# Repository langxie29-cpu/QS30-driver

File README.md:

# QS30 驱动 — 九位模块化（REV.A9）

> 最新进度（2026-11-15）：[24V重构项目](projects/QS30-9_24V/README.md)、[S06B资格审查报告](projects/QS30-9_24V/docs/SPRINT06B_REPORT.md)及[S06C续作计划](projects/QS30-9_24V/docs/S06C_PLAN.md)。24V-07未通过、08未进入，制造HOLD；[工程进展与知识书稿](output/nxt_book/书稿.md)。仿真大文件恢复见[归档说明](docs9/SIMULATION_ARCHIVES.md)。

> 最新实测入口（2026-11-10–11）：[Electrical Closure Sprint 01](docs9/ELECTRICAL_CLOSURE_SPRINT01.md)。DRC 753→698，ERC 0错误/364警告；高压启动/保护仍FAIL/HOLD，禁止投板。

> **当前基线：QS30-9 / REV.A（九位 3+3+3 模块化）**
> 先读 [`docs9/FINAL_REPORT9.md`](docs9/FINAL_REPORT9.md)（A–G 报告）与
> [`docs9/AUDIT.md`](docs9/AUDIT.md)（旧六位审计/架构差异）、[`docs9/GATES.md`](docs9/GATES.md)（G0–G5）。
>
> - 架构/网表/ERC9：`docs9/ARCHITECTURE.md`、`netlist9/`、`docs9/ERC9.md`（**36/36 PASS**，规则级）
> - 电源重算/OVP 容差/泄放：`docs9/POWER9.md`
> - 驱动比较 / BOM-A/B/C / 成本：`docs9/DRIVER_COMPARE.md`、`bom9/`、`docs9/COST9.md`
> - 接口与 90 路映射：`docs9/interface9.csv`、`docs9/channel_map9.csv`（位序 PROVISIONAL）
> - 机械/PCB 尺寸：`docs9/MECH9.md`（结论：三管共板不进 100 mm 档，需支架或 100×150）
> - 未冻结项：`HOLD_REGISTER9.md`；问题：`open_issues9.md`
> - **未经授权不下单、不打样、不释放 Gerber；未验证项不得标为通过。**
> - 旧六位 REV.A 设计完整保留为 Legacy（见文末"Legacy"与 `legacy/REV6/README.md`，commit `52eaa95`）。

---

## Legacy：六位 REV.A（REV6）原始文档

# QS30-6 REV.A — 六位静态辉光钟（ESP32-S3 / 南昌 QS30-1 / 立创EDA）

**工程状态：HOLD —— 可继续 PCB 预布局与实物验证，禁止投板、禁止生产放行。**
本仓库是 REV.A 的**可复现设计输入 + 已执行的仿真/检查证据**，不是已签审的完整 EDA 工程。

- 设计输入：`QS30-6_REV.A_ESP32_QS30-1_立创EDA工程交接_修订01.docx`（旧交接，已全程审查）
- 本基线：REV.A r1（2026-10-18）
- 规模：**227 个器件 / 736 个引脚 / 172 个网络 / 60 路数字阴极 / 2×HV5622**
- 自动一致性检查：**19 项全部 PASS（0 ERROR / 0 WARN）**，见 `docs/erc_report.md`

---

## 0. 交接入口

**先读 [`docs/HANDOVER.md`](docs/HANDOVER.md)**：交付物索引、证据分级、HOLD 解除路径、
从零复现验证结果与"禁止投板"结论。

## 1. 交付物索引

| 类别 | 文件 |
|---|---|
| 设计决策 | [`design_decisions.md`](design_decisions.md) |
| 未关闭问题 | [`open_issues.md`](open_issues.md) |
| 资料登记 | [`source_register.md`](source_register.md) |
| 变更记录 | [`REV_A_CHANGELOG.md`](REV_A_CHANGELOG.md) |
| HOLD 闸门 | [`HOLD_REGISTER.md`](HOLD_REGISTER.md) |
| 网表（逐引脚，权威） | [`netlist/QS30-6_REV.A_netlist.csv`](netlist/QS30-6_REV.A_netlist.csv) ｜ [`netlist/QS30-6_REV.A_nets.csv`](netlist/QS30-6_REV.A_nets.csv) ｜ [`netlist/QS30-6_REV.A_netlist.json`](netlist/QS30-6_REV.A_netlist.json) |
| BOM | [`bom/QS30-6_REV.A_BOM.csv`](bom/QS30-6_REV.A_BOM.csv) ｜ 已验证子集 [`bom/QS30-6_REV.A_BOM_verified_only.csv`](bom/QS30-6_REV.A_BOM_verified_only.csv) |
| 通道映射 | [`docs/channel_mapping.csv`](docs/channel_mapping.csv) ｜ [`docs/schematic/QS30-6_REV.A_通道映射表.png`](docs/schematic/QS30-6_REV.A_通道映射表.png) |
| QS30-1 脚号映射 | [`docs/qs30_1_pin_mapping.csv`](docs/qs30_1_pin_mapping.csv) |
| 原理图（连接表式分页图 + PDF） | [`docs/schematic/QS30-6_REV.A_原理图连接表.pdf`](docs/schematic/QS30-6_REV.A_原理图连接表.pdf)（11 页：系统框图 + 9 页分页连接表 + 通道映射表）｜ `docs/schematic/page_01.png` … `page_09.png` |
| 系统框图 | [`docs/schematic/QS30-6_REV.A_系统框图.png`](docs/schematic/QS30-6_REV.A_系统框图.png) |
| PCB 预布局 | [`docs/prelayout/QS30-6_REV.A_prelayout.png`](docs/prelayout/QS30-6_REV.A_prelayout.png) ｜ `.pdf` |
| BOM 数量汇总（114 组，含 DNP） | [`bom/QS30-6_REV.A_BOM_qty.csv`](bom/QS30-6_REV.A_BOM_qty.csv) |
| 逐页网络清单（立创EDA 录入用） | `netlist/by_sheet/{01_PWR,02_MCU,03_DRV,04_HV,05_TUBE,06_TP}_nets.csv` |
| 符号↔焊盘↔原厂脚号总表（H09 证据） | [`docs/symbol_footprint_mapping.csv`](docs/symbol_footprint_mapping.csv) |
| PCB 规则矩阵（H07 占位） | [`docs/pcb_rule_matrix.csv`](docs/pcb_rule_matrix.csv) |
| ERC 记录 | [`docs/erc_report.md`](docs/erc_report.md) |
| **DRC 预检（网表级，14/14 PASS）** | [`docs/drc_precheck.md`](docs/drc_precheck.md) ｜ [`drc_precheck.json`](docs/drc_precheck.json) ｜ 脚本 [`design/drc_precheck.py`](design/drc_precheck.py) |
| **HOLD 进度看板** | [`docs/hold_dashboard.md`](docs/hold_dashboard.md)（填写进度 + 关键路径） |
| **HOLD 签署与关闭联动（本次新增）** | 签署表 [`docs/HOLD_SIGNOFF.csv`](docs/HOLD_SIGNOFF.csv) ｜ 报告 [`docs/hold_signoff_report.md`](docs/hold_signoff_report.md) |
| **HOLD 证据模板与自动校验** | 模板 [`docs/evidence/`](docs/evidence/README.md)（10 个 CSV，含期望值与判据）｜ 校验 [`design/evidence_check.py`](design/evidence_check.py) ｜ 状态报告 [`docs/hold_closure_report.md`](docs/hold_closure_report.md) ｜ 框架自测 [`docs/evidence_selftest.md`](docs/evidence_selftest.md) |
| 立创EDA 构建步骤 | [`docs/lceda_implementation_guide.md`](docs/lceda_implementation_guide.md) |
| 上电验证计划 | [`docs/test_plan.md`](docs/test_plan.md) |
| 升压/OVP 仿真 | [`sim/README.md`](sim/README.md) ｜ 结果 `sim/results/`（6 张图 + 10 份 CSV + summary.json + convergence） |
| **平均模型闭环仿真** | `sim/boost_averaged.cir` ／ `sim/boost_averaged_steps.cir` ｜ 结果 [`sim/results/spice_averaged_closed_loop.png`](sim/results/spice_averaged_closed_loop.png) |
| **OVP 保护逻辑 SPICE** | `sim/boost_ovp_logic.cir` ｜ 结果 [`sim/results/spice_ovp_latch.png`](sim/results/spice_ovp_latch.png)（触发/锁存/泄放/复位/再触发，7 项判据） |
| **OVP 时序回归（本次新增）** | 复位脉冲宽度/锁存保持扫描：`design/ovp_timing_scan.py` ｜ [`docs/ovp_timing.md`](docs/ovp_timing.md) |
| **测试计划一致性检查** | `docs/test_plan.csv`（37 项机读）＋ `design/test_plan_check.py` ｜ [`docs/test_plan_check.md`](docs/test_plan_check.md) 5/5 PASS |
| **固件约束清单（本次新增）** | `design/firmware_constraints.py` 派生 ｜ [`docs/firmware_constraints.md`](docs/firmware_constraints.md) ／ [`.json`](docs/firmware_constraints.json)（8 控制脚、64 位帧、13 条约束） |
| **文档数字一致性检查** | `design/doc_number_check.py` ｜ [`docs/doc_consistency.md`](docs/doc_consistency.md) 5/5 PASS |
| **BOM 选型复核** | `design/bom_review.py` ｜ [`docs/bom_review.md`](docs/bom_review.md)（14 关键件降额/替代料，5/5 PASS） |
| **热/浪涌复核（本次新增）** | `design/thermal_review.py` ｜ [`docs/thermal_review.md`](docs/thermal_review.md)（HV5622 温升 0.7–6.3 °C；浪涌 I²t 0.0010 A²s） |
| **投板前检查清单（本次新增）** | `design/preflight_checklist.py` ｜ [`docs/preflight_checklist.md`](docs/preflight_checklist.md)（**RELEASE BLOCKED**：机器检查 11/11，HOLD 0/9） |
| **SPICE 子集求解器（仓库自带）** | [`sim/minispice.py`](sim/minispice.py) ｜ 验证网表 `sim/spice_tests/` ｜ 结果 [`sim/results/spice_validation.md`](sim/results/spice_validation.md) ｜ [`spice_boost_summary.json`](sim/results/spice_boost_summary.json) ｜ 波形 [`spice_boost_waveforms.png`](sim/results/spice_boost_waveforms.png) |
| 审查包（合并 PDF，15 页） | [`docs/QS30-6_REV.A_审查包.pdf`](docs/QS30-6_REV.A_审查包.pdf) |
| QS30-1 符号建库说明 / 规格 | [`symbols/README.md`](symbols/README.md) ｜ [`symbols/QS30-1_symbol_spec.json`](symbols/QS30-1_symbol_spec.json) |
| 管座封装草案（TBD，H03） | [`symbols/QS30-1_socket_footprint_draft.json`](symbols/QS30-1_socket_footprint_draft.json) ｜ 1:1 校对页 [`docs/footprint/QS30-1_管座_1比1校对页.pdf`](docs/footprint/QS30-1_管座_1比1校对页.pdf) ｜ 实测工作表 [`docs/footprint/H03_管座实测工作表.md`](docs/footprint/H03_管座实测工作表.md) |
| 仿真收敛性证据 | [`sim/results/convergence.md`](sim/results/convergence.md) ｜ [`.json`](sim/results/convergence.json) |
| 原始资料证据（扫描/渲染） | [`docs/source_scans/`](docs/source_scans/)（QS30-1 原厂页、HV5622 引脚表/真值表、CD40109B 引脚注记、TL431/74HC08/UC3843/USBLC6 引脚图） |
| 设计数据库与生成器 | [`design/model.py`](design/model.py) ｜ [`design/sheet_lv.py`](design/sheet_lv.py) ｜ [`design/sheet_hv.py`](design/sheet_hv.py) ｜ [`design/build.py`](design/build.py) ｜ [`design/render.py`](design/render.py) ｜ [`design/sim_boost.py`](design/sim_boost.py) |

## 2. 关键结论（VERIFIED）

1. **QS30-1 电极映射由原厂说明书直接确定**：2=A；3=K0、4=K9、5=K8、6=K7、7=K6、9=K5、
   10=K4、11=K3、12=K2、13=K1；**1、8 脚为非显示内部电极，悬空不接**。无小数点/冒号电极。
2. **QS30-1 工作参数（原厂基本参数表）**：起辉 ≤150 V、熄灭 ≥100 V、Ea=170 V、Ik=1.5/2.25/3 mA、
   Ra=20 kΩ、寿命 1000 h、φ30.2、总高 34±1.5、管基 GB 787-74 J13-1A。
3. **HV5622 每片 32 路输出** → 60 路需求用 **2 片（64 路）**，不是 3 片；帧长 **64 bit**。
4. **HV5622 危险态**：POL=低且 BL=低 → 全部输出导通。故 POL 硬件固定接 DRV_VDD，
   BL 在 12 V 域下拉（默认消隐），并且高压母线受 DRV_PG 门控。
5. **ESP32-S3-WROOM-1 焊盘 1–41、USB D−/D+ = GPIO19/20、strapping = GPIO0/3/45/46** 与交接表一致。
6. **TL431（DBZ/SOT-23-3）引脚是 1=CATHODE、2=REF、3=ANODE**（旧稿按 SOT-23-5 顺序写错，已修正）。

## 3. 本 REV.A 已实施的设计（要点）

- 电源：12 V → 5.08 V（TPS54202）→ 双肖特基 OR → 3.315 V（SY8089A）；DRV_VDD 由默认关断的
  高边开关供给；3.3 V 按 800 mA 分配；USB-C 仅逻辑供电（≤500 mA 限制写入固件要求）。
- 门控：EXT12_PG(10.80 V)、3V3_PG(3.107 V)、DRV_PG(10.41 V)、FAULT_OK → 74HC08 →
  DRV_VDD_EN / HV_EN；MCU 只能请求（GPIO16），复位/掉电默认全关。
- 高压：UC3843 升压 78 kHz → **172.18 V**；6×（2×10 kΩ/2 W）阳极限流；OVP **198.8 V**
  独立比较器 + 分立 SCR 锁存 + GPIO18 受控复位；200 kΩ 泄放（仿真 172→50 V 用时 3.84 s）。
- 驱动：2×HV5622（PQFP-44）+ 2×CD40109B 电平转换；60 路阴极映射表 + walking-one 验证要求。
- 布局：230×120 mm 建议外形、4 层、天线禁布/高压分区/隔离带，见预布局图。

## 4. 仿真结论摘要

### 4.1 功率级 SPICE（仓库自带 `sim/minispice.py`，已执行）

| 项目 | SPICE 结果 | 解析/理论 | 偏差 |
|---|---|---|---|
| 稳态输出 | **171.99 V** | 171.95 V（DCM 公式） | +0.02% |
| 电感峰值电流 | **503 mA** | 510 mA | -1.4% |
| 输出纹波（单周期） | **8.7 mVpp** | 9.0 mVpp | -3% |
| 效率（h=10 ns） | **95.9%** | 器件损耗估算 ≈96% | — |
| Coss 敏感性 | 100 pF 开关电容 → **91.0%** | ½CV²f≈0.12 W | 5 个百分点 |

求解器自检：RC（1.8 mV）、RL（0.46 mA）、二极管（5.6e-17 V）、B 源（1.0e-2 V）全部 PASS。
厂商 ngspice 网表 `sim/boost_uc3843.cir` **未执行**（环境无 ngspice）。

### 4.2 闭环/保护行为（`design/sim_boost.py`，行为模型，Ts/80）

| 场景 | 结果 |
|---|---|
| 启动（六管） | 172.08 V，过冲 180.75 V（+4.97%），未触发 OVP；浪涌峰值 2.91 A |
| 六管稳态 | 172.08 V，纹波 1.1 Vpp，效率 77.6% |
| 空载（消隐） | 172.19 V，过冲 187.4 V（+8.8%） |
| 反馈开路 | 198.80 V 触发 OVP 并锁存（142 ms）；受控复位后 558 ms 再触发 |
| 断电泄放 | 172 V → 50 V：**3.84 s** |
| 输出短路 10 Ω | 电流限流，输出 10.8 V，OVP 不误动 |

> 模型边界：行为级、非器件级 SPICE；开关损耗/振铃/反向恢复/温升未建模。ngspice 参考网表
> `sim/boost_uc3843.cir` **未执行**（本机无 ngspice/LTspice）。

## 5. 当前阻塞（必须优先关闭）

`H01` 旧基线、`H02` 实物管脚/工作点、`H03` 管座与封装、`H04` 驱动时序/位序、
`H05` 供电实测、`H06` 高压实测、`H07` 高压间距标准 → 任一未关闭**不得投板**；
`H08` RF、`H09` EDA 验收未关闭 **不得生产**。详见 `HOLD_REGISTER.md` / `open_issues.md`。

HOLD 关闭的证据模板已生成（`docs/evidence/`），填表后运行 `python design/evidence_check.py`
即可自动判断「未提交/部分/完整/失败」，通过后才进入人工签署（当前 0/7 已提交，符合"无实物数据"现状）。

最需要立即处理的三个务实动作：
1. 购样 13 脚管座并实测（H03）——这是唯一阻止 PCB 封装的机械项。
2. 单管夹具逐脚点亮 QS30-1 并记录 U_tube/I（H02/H06）。
3. walking-one 位序测试（H04）——固件 LUT 冻结前必须完成。

## 6. 复现方式

```powershell
cd design
python build.py        # 生成 netlist/、bom/、docs/*.csv、docs/erc_report.md
python render.py       # 生成 docs/schematic/、docs/prelayout/
python export_extra.py # 生成 BOM 数量汇总、逐页网络清单、符号/焊盘总表、规则矩阵
python footprint_draft.py  # 生成管座封装草案 JSON + 1:1 校对页
python review_package.py   # 生成 docs/QS30-6_REV.A_审查包.pdf
python sim_boost.py        # 生成 sim/results/（开关级仿真与图表）
python sim_check.py        # 行为模型步长收敛性检查
python sim/spice_validation.py  # 执行 minispice：解析解自检 + 升压功率级 SPICE + 步长/Coss 敏感性
python evidence_templates.py   # 生成 HOLD 关闭证据模板（期望值自动填入）
python evidence_check.py       # 校验已提交证据（未提交/部分/完整/失败）
python evidence_selftest.py    # 证据校验框架自测（合成数据，证明判据有效）
python hold_signoff.py         # HOLD 自动证据 + 人工签署联动（CLOSED 需两者同时满足）
python ovp_timing_scan.py      # OVP 复位脉宽/锁存保持扫描（约 90 s）
python test_plan_check.py      # 测试计划 ↔ 证据模板一致性（37 项，5 条规则）
python firmware_constraints.py # 从网表/映射表派生固件约束（GPIO/帧长/位序）
python doc_number_check.py     # 跨文档关键数字一致性（防 95.8%/158ms 类漂移）
python bom_review.py           # 关键器件降额/替代料/封装状态复核（14 件）
python thermal_review.py       # HV5622 功耗/温升估算 + PPTC 启动浪涌 I²t
python preflight_checklist.py  # 投板前汇总（HOLD + 全部机器检查 → RELEASE BLOCKED）
```

依赖：Python 3.12 + numpy + matplotlib（均已在本环境验证可用）。
设计数据唯一来源是 `design/*.py` 中的器件/连接定义；网表、BOM、连接表式原理图、
映射表均由同一份数据生成，避免"图-表-网表"不一致。

## 7. 环境限制与诚实声明

- 当前环境**没有**立创EDA、LTspice、ngspice；已验证：KiCad 只能通过 winget 安装且
  需要管理员权限（本会话非管理员，安装无法完成），ngspice 的 SourceForge 下载被 403 拦截。
  作为替代，仓库自带 `sim/minispice.py`（SPICE 子集求解器），已用**解析解**自检通过并
  **实际执行了升压功率级 SPICE 网表**（见 `sim/results/spice_validation.md`）；
  厂商 ngspice 网表 `sim/boost_uc3843.cir` 仍未执行。
  因此**没有**生成可编辑的立创EDA 工程，
  也**没有**执行原生 ERC/DRC 与 SPICE。替代交付物为：完整网表、BOM、封装定义要求、
  连接表式分页原理图（PDF）、立创EDA 逐步构建说明、可运行的 Python 开关级仿真。
- 管座 PCB 封装**未定义尺寸**（H03）；预布局只是分区与约束优先级，不是可投板版图。
- 全部器件状态见 BOM 的 `status` 列：`VERIFIED` / `PROVISIONAL` / `HOLD`；
  `BOM_verified_only.csv` 仅为资料已核对子集，**不是可下单清单**。

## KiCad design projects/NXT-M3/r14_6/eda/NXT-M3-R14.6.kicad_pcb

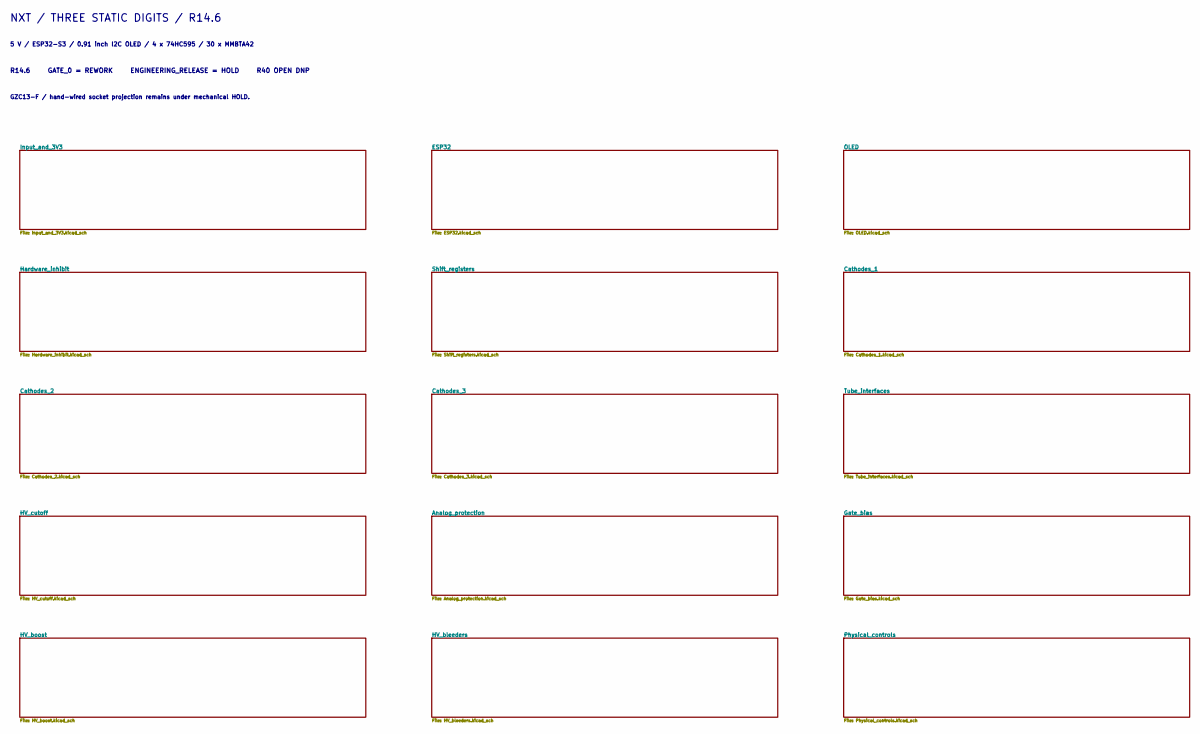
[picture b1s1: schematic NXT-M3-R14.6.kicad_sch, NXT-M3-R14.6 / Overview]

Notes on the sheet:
NXT / THREE STATIC DIGITS / R14.6
5 V / ESP32-S3 / 0.91 inch I2C OLED / 4 x 74HC595 / 30 x MMBTA42
R14.6 GATE_0 = REWORK ENGINEERING_RELEASE = HOLD R40 OPEN DNP
GZC13-F / hand-wired socket projection remains under mechanical HOLD.

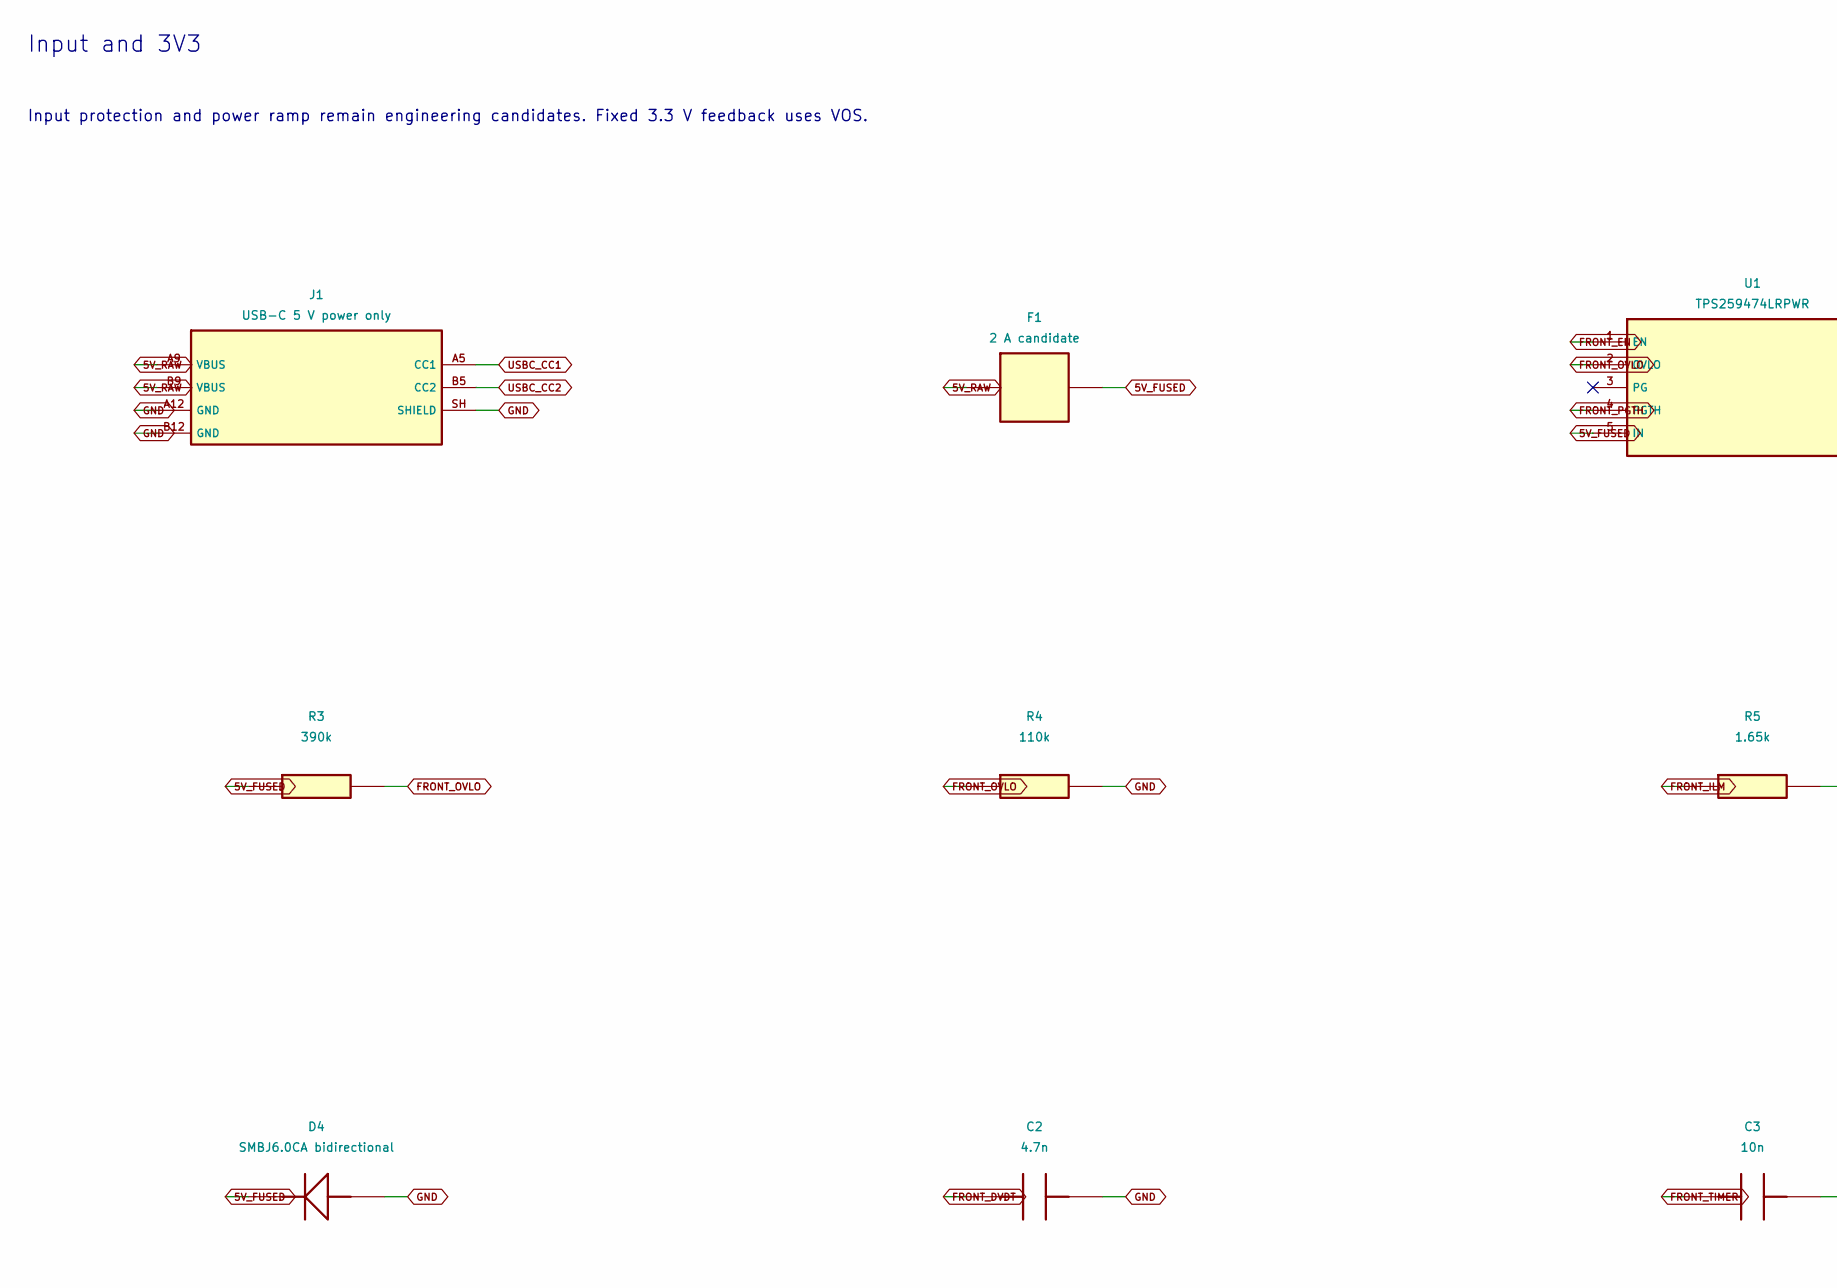
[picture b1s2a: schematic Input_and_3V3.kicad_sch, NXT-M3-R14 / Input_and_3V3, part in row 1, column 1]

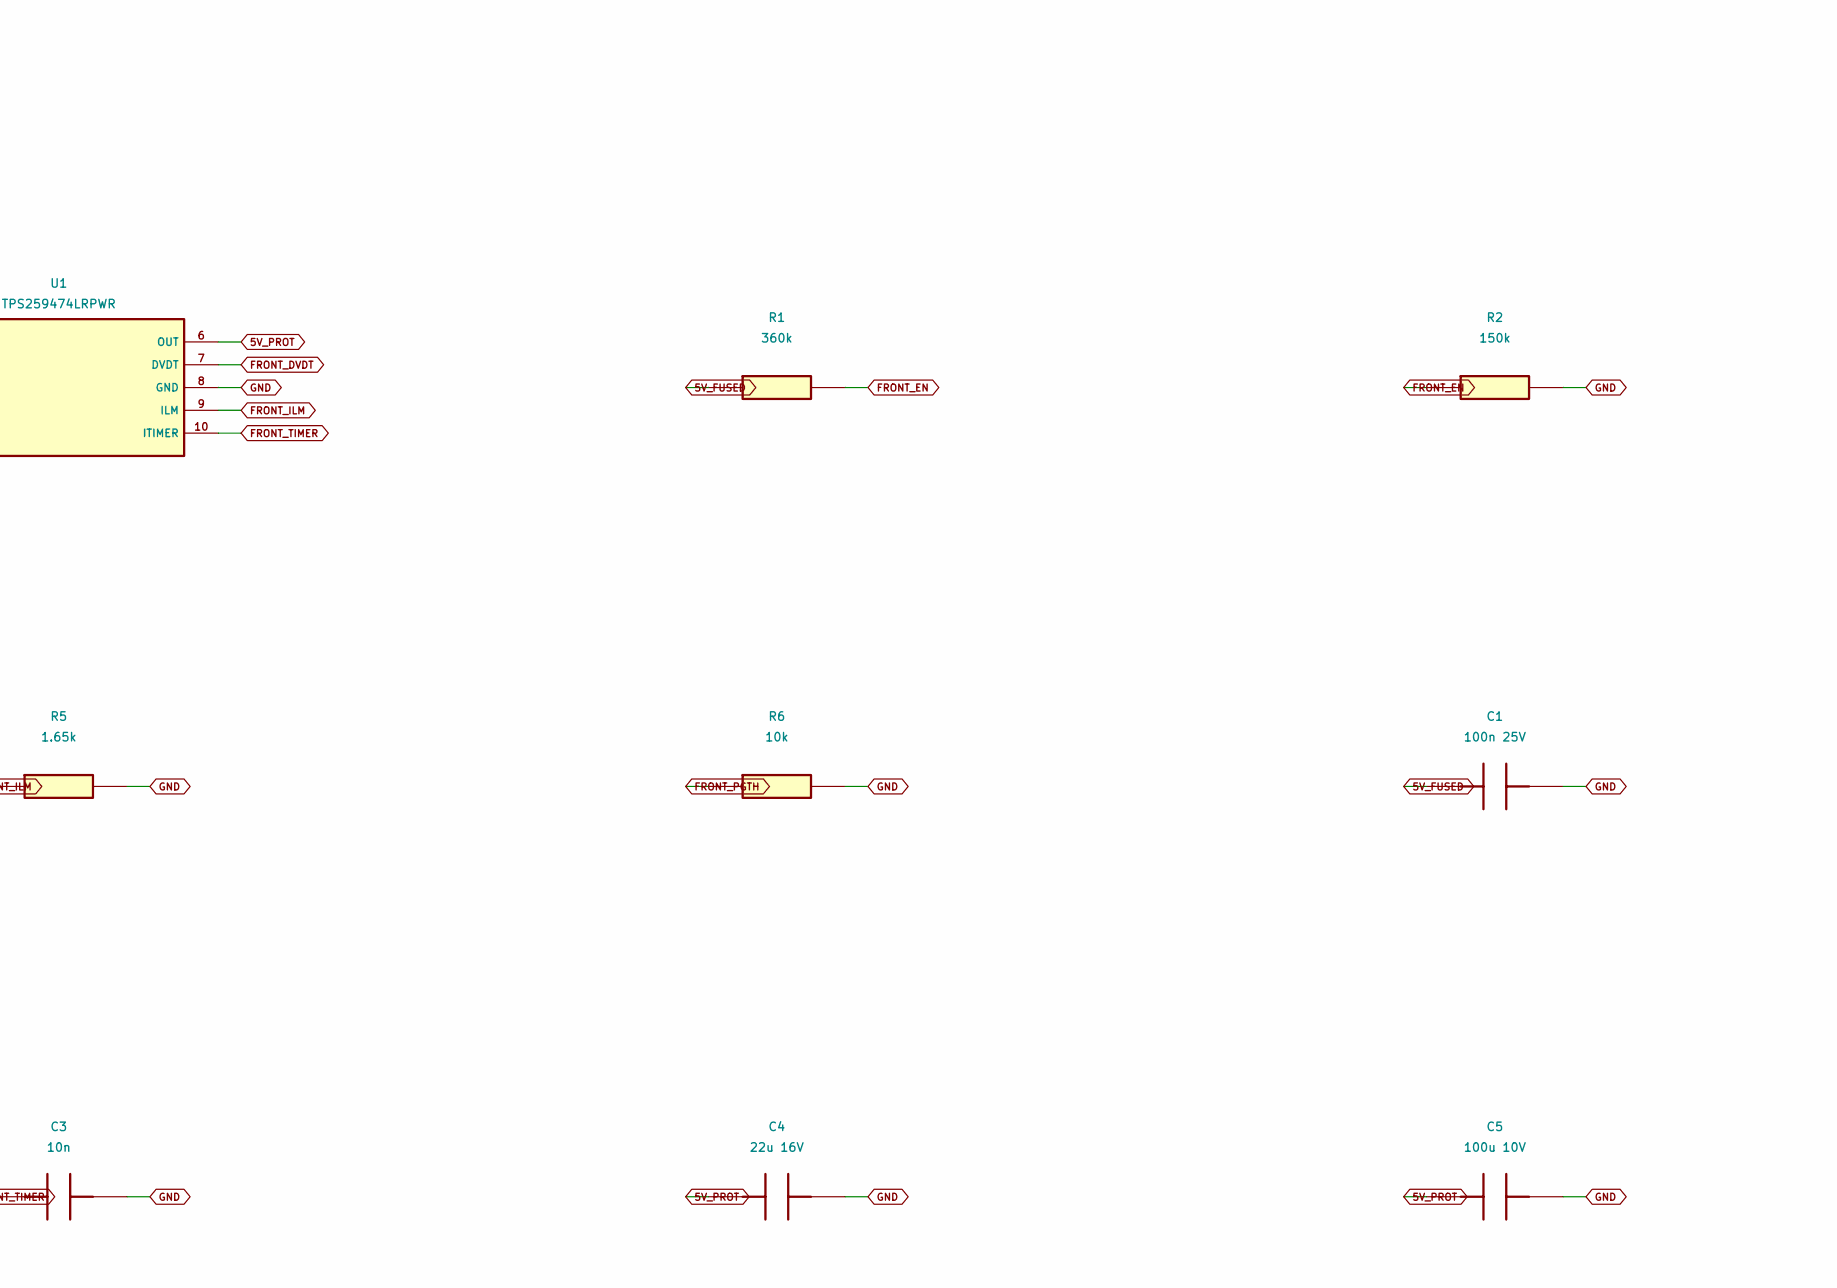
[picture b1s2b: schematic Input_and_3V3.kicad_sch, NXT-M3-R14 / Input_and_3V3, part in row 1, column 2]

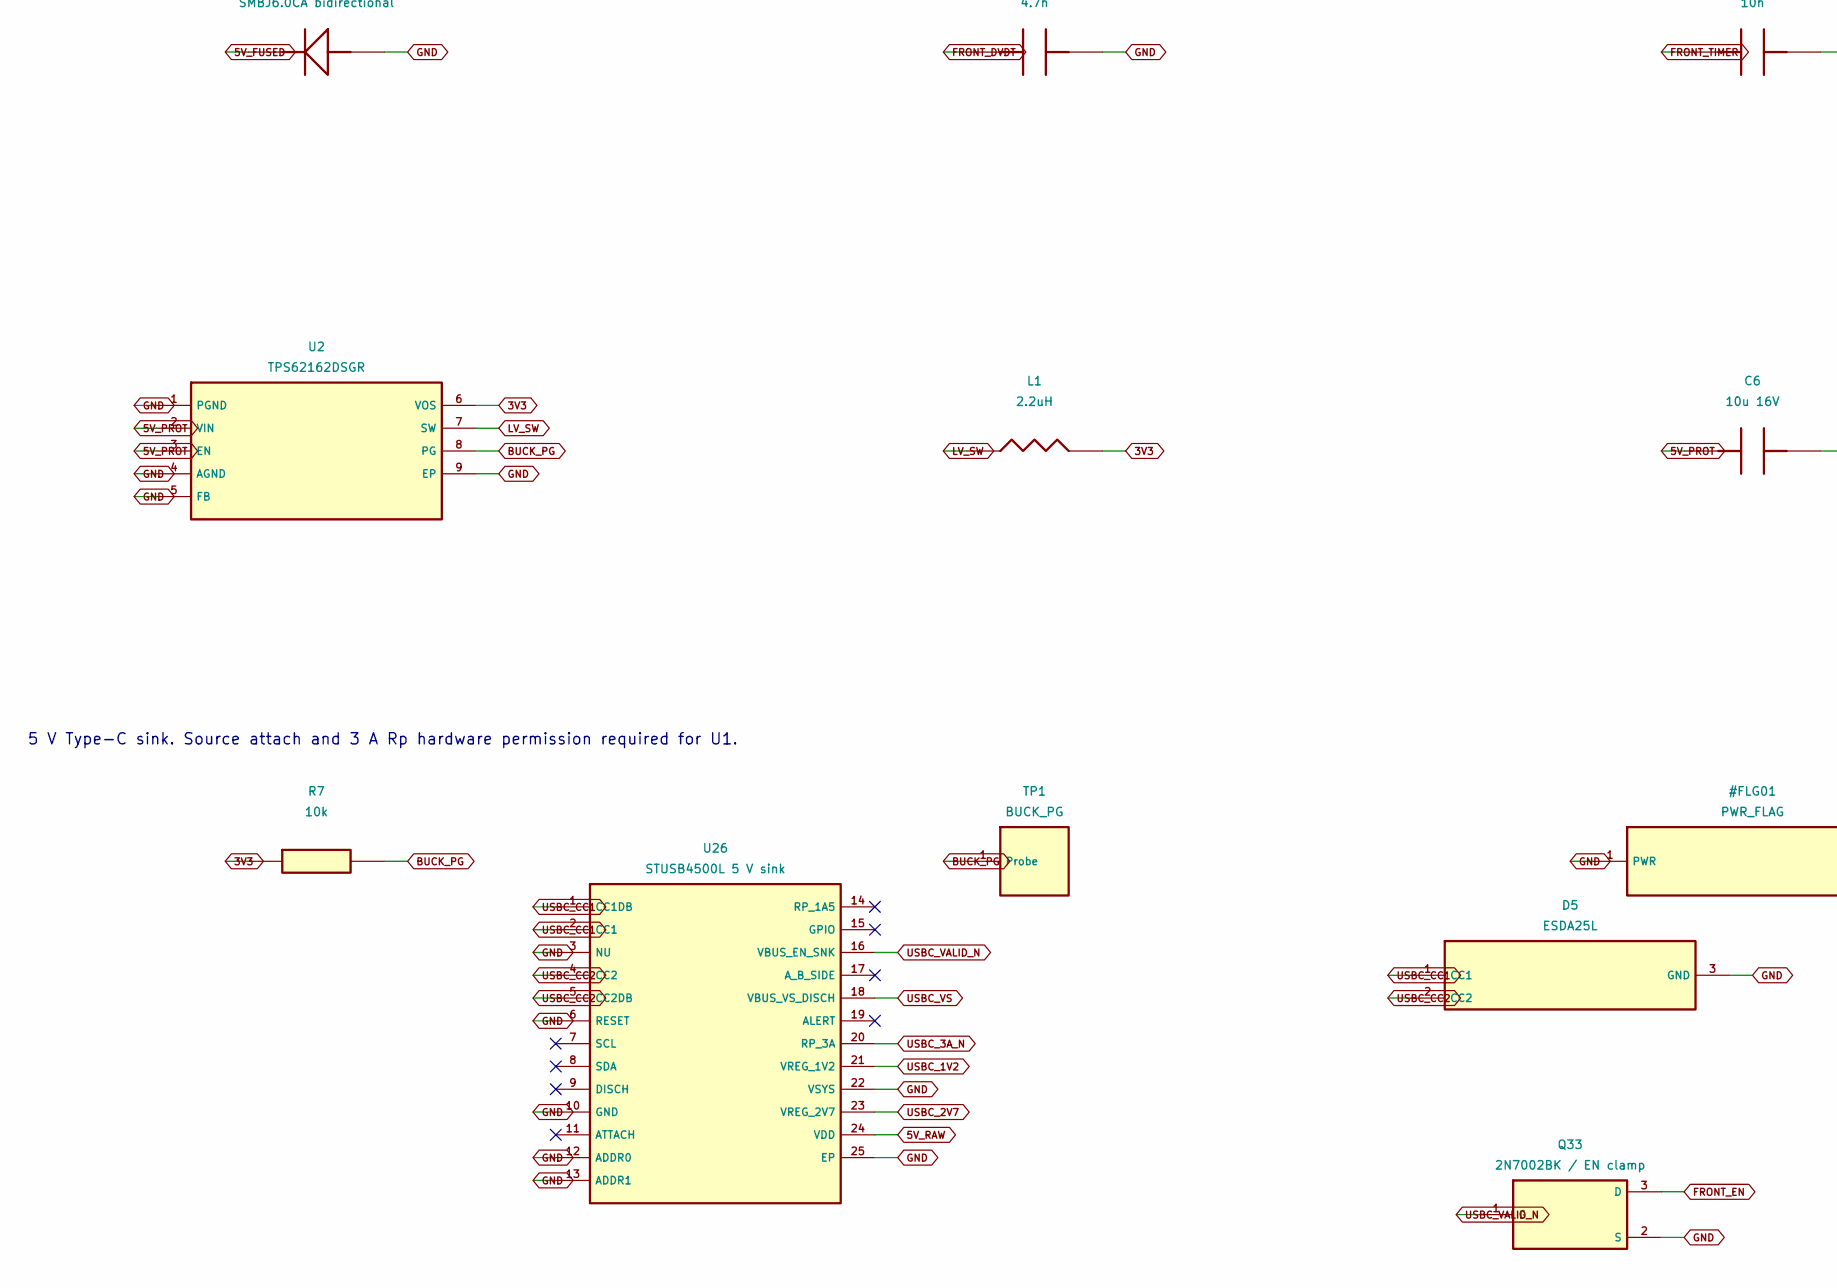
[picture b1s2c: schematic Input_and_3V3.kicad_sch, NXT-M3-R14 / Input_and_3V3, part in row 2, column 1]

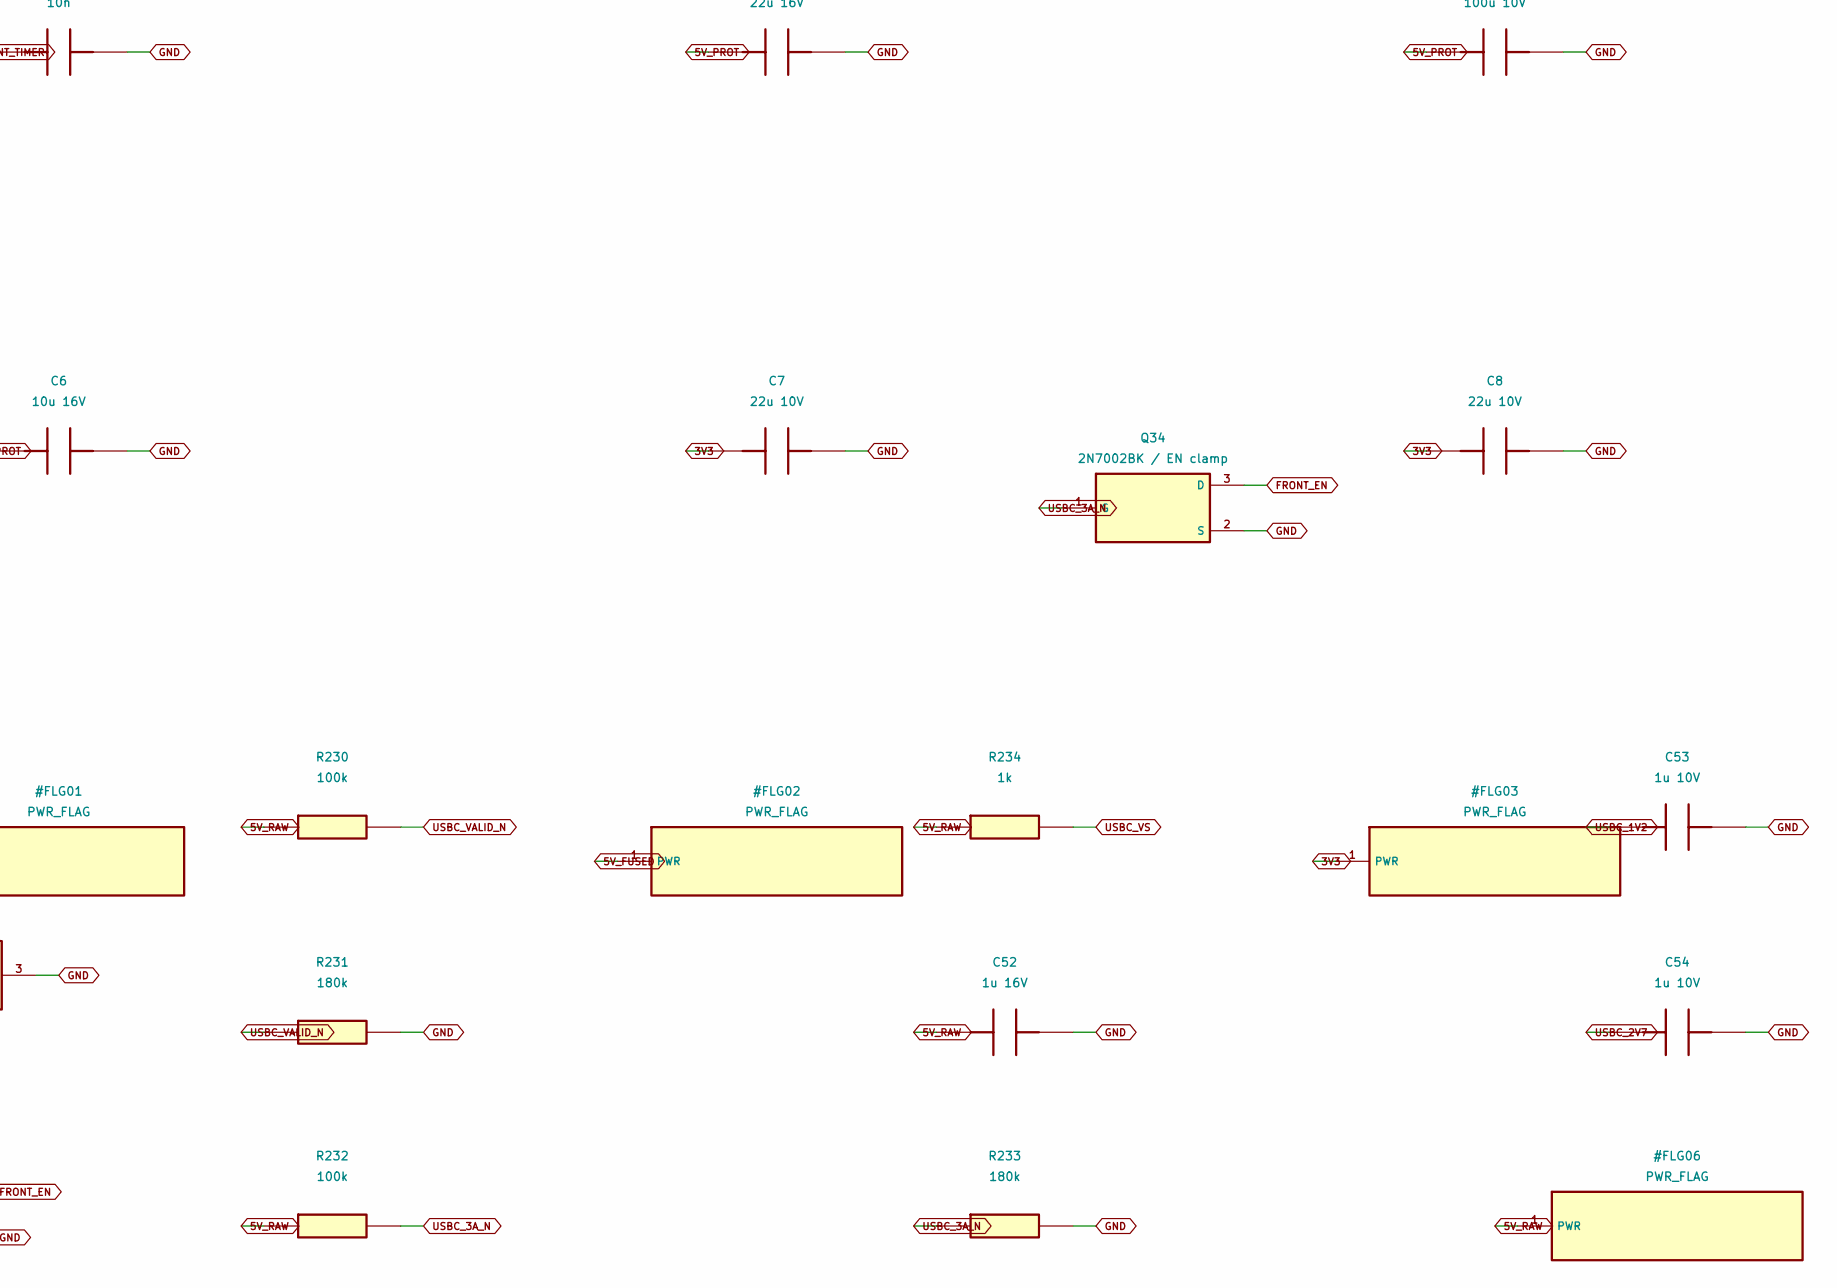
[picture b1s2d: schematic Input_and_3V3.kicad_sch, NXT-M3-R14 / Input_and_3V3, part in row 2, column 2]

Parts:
C1: 100n 25V; C_0603_1608Metric
C2: 4.7n; C_0603_1608Metric
C3: 10n; C_0603_1608Metric
C4: 22u 16V; C_1206_3216Metric
C5: 100u 10V; CP_Elec_6.3x5.8
C6: 10u 16V; C_0805_2012Metric
C7, C8: 22u 10V; C_1206_3216Metric
C52: 1u 16V; C_0603_1608Metric
C53, C54: 1u 10V; C_0603_1608Metric
D4: SMBJ6.0CA bidirectional; D_SMB; MPN SMBJ6.0CA
D5: ESDA25L; SOT-23; MPN ESDA25L
F1: 2 A candidate; Fuse_1206_3216Metric; MPN 0467002.NR
J1: USB-C 5 V power only; USB_C_Receptacle_GCT_USB4125-xx-x_6P_TopMnt_Horizontal; MPN USB4125-GF-A
L1: 2.2uH; L_Bourns-SRN4018; MPN SRN4018-2R2M
Q33, Q34: 2N7002BK / EN clamp; SOT-23; MPN 2N7002BK,215
R1: 360k; R_0603_1608Metric
R2: 150k; R_0603_1608Metric
R3: 390k; R_0603_1608Metric
R4: 110k; R_0603_1608Metric
R5: 1.65k; R_0603_1608Metric
R6, R7: 10k; R_0603_1608Metric
R230, R232: 100k; R_0603_1608Metric
R231, R233: 180k; R_0603_1608Metric
R234: 1k; R_0603_1608Metric
TP1: BUCK_PG; TestPoint_Pad_D1.5mm
U1: TPS259474LRPWR; TI_RPW0010A; MPN TPS259474LRPWR
U2: TPS62162DSGR; Texas_DSG0008A_WSON-8-1EP_2x2mm_P0.5mm_EP0.9x1.6mm; MPN TPS62162DSGR
U26: STUSB4500L 5 V sink; QFN-24-1EP_4x4mm_P0.5mm_EP2.6x2.6mm; MPN STUSB4500LQTR

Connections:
3V3: C7.1, C8.1, L1.2, R7.1, U2.6 (VOS); also elsewhere on the board
5V_FUSED: C1.1, D4.1 (K), F1.2, R1.1, R3.1, U1.5 (IN)
5V_PROT: C4.1, C5.1, C6.1, U1.6 (OUT), U2.2 (VIN), U2.3 (EN); also elsewhere on the board
5V_RAW: C52.1, F1.1, J1.A9 (VBUS), J1.B9 (VBUS), R230.1, R232.1, R234.1, U26.24 (VDD)
BUCK_PG: R7.2, TP1.1, U2.8 (PG)
FRONT_DVDT: C2.1, U1.7 (DVDT)
FRONT_EN: Q33.3 (D), Q34.3 (D), R1.2, R2.1, U1.1 (EN)
FRONT_ILM: R5.1, U1.9 (ILM)
FRONT_OVLO: R3.2, R4.1, U1.2 (OVLO)
FRONT_PGTH: R6.1, U1.4 (PGTH)
FRONT_TIMER: C3.1, U1.10 (ITIMER)
GND: C1.2, C2.2, C3.2, C4.2, C5.2, C6.2, C7.2, C8.2, C52.2, C53.2, C54.2, D4.2 (A), D5.3 (GND), J1.A12 (GND), J1.B12 (GND), J1.SH (SHIELD), Q33.2 (S), Q34.2 (S), R2.2, R4.2, R5.2, R6.2, R231.2, R233.2, U1.8 (GND), U2.1 (PGND), U2.4 (AGND), U2.5 (FB), U2.9 (EP), U26.3 (NU), U26.6 (RESET), U26.10 (GND), U26.12 (ADDR0), U26.13 (ADDR1), U26.22 (VSYS), U26.25 (EP); also elsewhere on the board
LV_SW: L1.1, U2.7 (SW)
USBC_1V2: C53.1, U26.21 (VREG_1V2)
USBC_2V7: C54.1, U26.23 (VREG_2V7)
USBC_3A_N: Q34.1 (G), R232.2, R233.1, U26.20 (RP_3A)
USBC_CC1: D5.1 (CC1), J1.A5 (CC1), U26.1 (CC1DB), U26.2 (CC1)
USBC_CC2: D5.2 (CC2), J1.B5 (CC2), U26.4 (CC2), U26.5 (CC2DB)
USBC_VALID_N: Q33.1 (G), R230.2, R231.1, U26.16 (VBUS_EN_SNK)
USBC_VS: R234.2, U26.18 (VBUS_VS_DISCH)

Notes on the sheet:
Input and 3V3
Input protection and power ramp remain engineering candidates. Fixed 3.3 V feedback uses VOS.
5 V Type-C sink. Source attach and 3 A Rp hardware permission required for U1.
